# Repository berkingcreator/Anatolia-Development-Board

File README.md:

# Anatolia Geliştirme Kart Serisi

**Anatolia Geliştirme Kart Serisi**, açık kaynaklı mikrodenetleyici mimarilerini ve AVR (ATmega ve ATtiny) çekirdeklerini temel alan, yerli ve modüler bir geliştirme donanımı ailesidir. Düşük güç tüketimi gerektiren gömülü sistemlerden lojik devre simülasyonlarına, giyilebilir teknolojilerden hafif otonom modüllere kadar geniş bir yelpazede esnek çözümler sunar.

---

## 🚀 Öne Çıkan Özellikler

* **Açık Kaynak Donanım & Mimari:** Tamamen açık kaynaklı şematik ve donanım tasarımı ile özelleştirilebilir yapı.
* **Geniş Çekirdek Desteği:** İhtiyaca göre ölçeklenebilen ATmega328P ve ATtiny85 / ATtiny84 tabanlı yüksek verimli mikrodenetleyici entegrasyonu.
* **Kompakt Form Faktörü:** Minimal alan kaplayan, breadboard ve özel PCB uygulamalarına kolayca entegre edilebilir yapı.
* **Dahili Bootloader Desteği:** Optiboot ve Micronucleus / V-USB bootloader destekleri sayesinde harici programlayıcıya ihtiyaç duymadan USB üzerinden doğrudan kod yükleme.
* **Esnek G/Ç (GPIO) ve PWM:** Kart boyutuna göre optimize edilmiş dahili ADC okuma, SPI/I2C haberleşme ve PWM çıkış yeteneği.

---

## 🛠️ Kart Modelleri

* **Anatolia UNO R1 (ATmega328P):** Serinin temel amiral gemisi. Karmaşık prototipleme süreçleri, sensör ağları ve geniş G/Ç (GPIO) kapasitesi gerektiren standart projeler için geliştirilmiş çok yönlü ana geliştirme kartı.
* **Anatolia Kart G (ATtiny2313A):** Serinin 6 gen şeklindeki kartı. Giyilebilir teknolojiler için ideal.
* **Anatolia Pro Mini (ATtiny85):** Düşük güç tüketimi ve alan kısıtlaması olan gömülü projeler ile özel PCB tasarımlarına doğrudan entegre edilmek için ideal, ultra kompakt geliştirme modülü.
* **Anatolia Micro (ATtiny85):** Giyilebilir teknolojiler, minyatür sistemler ve doğrudan USB programlama gerektiren hızlı pratik çözümler için optimize edilmiş mikro boyutlu kart.
* **Anatolia Lite (ATtiny44A):** Serinin en küçük üyesi. Micro USB. Arduino İDE uyumlu.
* **Anatolia Nano (ATtiny2313A):** Nano boyutlarında tam güç!
*  **Anatolia Micro R2 (ATmega328P):** Anatolia Uno'nun gücü küçük bir kartta! Küçük projeler için ideal.

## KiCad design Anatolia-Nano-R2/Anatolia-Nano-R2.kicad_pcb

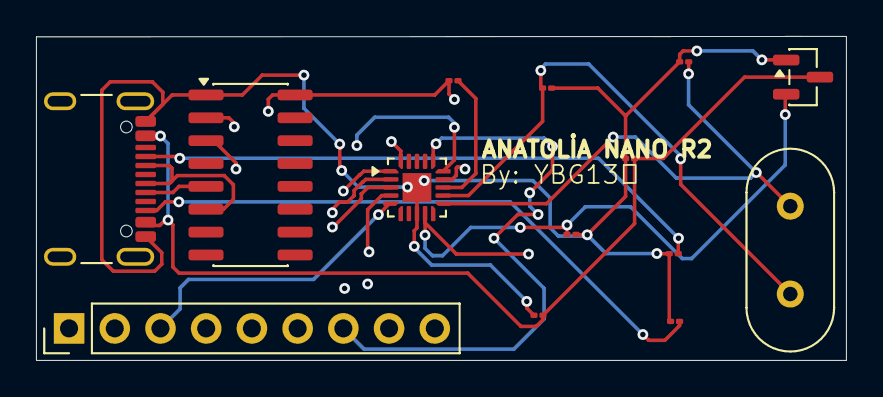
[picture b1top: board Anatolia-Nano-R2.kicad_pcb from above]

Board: 4 copper layers, 45.0 x 18.0 mm, 14 parts (0 on the bottom side), 19 nets.

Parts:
C1, C2: 22pF; C_01005_0402Metric
C3: 100nF; C_01005_0402Metric
C4, C5: 1µF; C_01005_0402Metric
J1: USB_C_Receptacle_USB2.0_16P; USB_C_Receptacle_GCT_USB4105-xx-A_16P_TopMnt_Horizontal
J2: Conn_01x09; PinHeader_1x09_P2.54mm_Vertical
R1: 10k; R_01005_0402Metric
R2, R3: 5.1k; R_01005_0402Metric
U1: ATtiny841-MM; QFN-20-1EP_3x3mm_P0.45mm_EP1.6x1.6mm
U2: CH340G; SOIC-16_3.9x9.9mm_P1.27mm
U3: MCP1700x-330xxTT; SOT-23
Y1: 8MHz; Crystal_HC49-4H_Vertical

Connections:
GND: C1.1, C2.2, C3.1, C4.1, C5.2, J1.A1 (GND), J1.A12 (GND), J1.B1 (GND), J1.B12 (GND), J2.2, R2.1, R3.1, U1.8 (GND), U1.21 (GND), U2.1 (GND), U3.1 (GND)
unnamed: J1.A5 (CC1), R2.2
unnamed: J1.B5 (CC2), R3.2
unnamed: C5.1, J2.1, R1.1, U1.9 (VCC), U2.16 (VCC), U3.2 (VO)
unnamed: J2.3, U1.5 (AREF/PA0)
unnamed: J2.4, U1.2 (PA3)
unnamed: J2.5, U1.1 (PA4)
unnamed: J2.6, U1.20 (PA5)
unnamed: J2.7, U1.16 (PA6)
unnamed: J2.8, U1.15 (PA7)
unnamed: J2.9, U1.14 (PB2)
unnamed: U1.4 (PA1), U2.3 (RXD)
unnamed: U1.3 (PA2), U2.2 (TXD)
unnamed: C1.2, U1.11 (XTAL1/PB0), Y1.2
unnamed: C2.1, U1.12 (XTAL2/PB1), Y1.1
unnamed: R1.2, U1.13 (~RESET/PB3)
unnamed: J1.A6 (D+), J1.B6 (D+), U2.5 (UD+)
unnamed: J1.A7 (D-), J1.B7 (D-), U2.6 (UD-)
VCC: C3.2, C4.2, J1.A4 (VBUS), J1.A9 (VBUS), J1.B4 (VBUS), J1.B9 (VBUS), U3.3 (VI)

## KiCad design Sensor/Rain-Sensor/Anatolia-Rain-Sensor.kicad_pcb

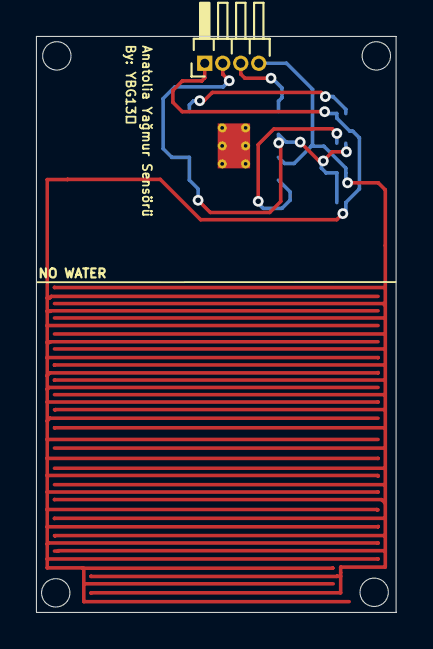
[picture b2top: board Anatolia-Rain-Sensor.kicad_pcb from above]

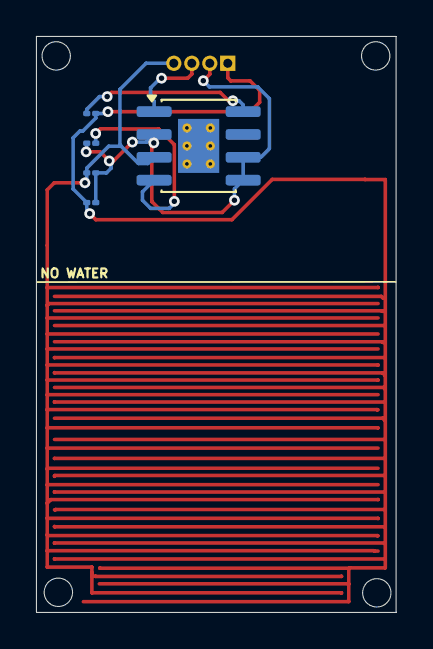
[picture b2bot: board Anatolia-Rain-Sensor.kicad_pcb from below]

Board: 2 copper layers, 20.0 x 32.0 mm, 6 parts (5 on the bottom side), 6 nets.

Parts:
C1, C2: 100nF; C_01005_0402Metric
J1: Conn_01x04_Pin; PinHeader_1x04_P1.00mm_Horizontal
R1, R2: 10K; R_01005_0402Metric
U1: LM393; SOIC-8-1EP_3.9x4.9mm_P1.27mm_EP2.29x3mm_ThermalVias

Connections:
/3: J1.4, R1.1, U1.3 (+)
/D0: J1.3, U1.1
GND: C2.1, J1.2, R1.2, R2.2, U1.2 (-), U1.5 (+), U1.6 (-)
unnamed: C1.1, U1.8 (V+)
unnamed: C2.2, U1.4 (V-)
VCC: C1.2, J1.1, R2.1

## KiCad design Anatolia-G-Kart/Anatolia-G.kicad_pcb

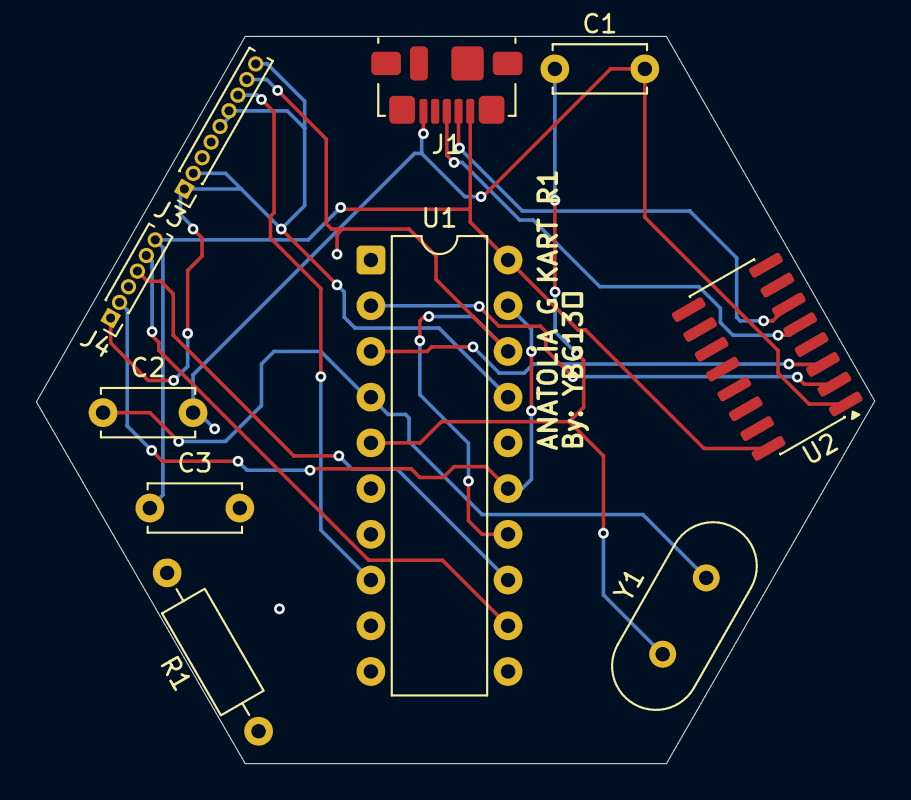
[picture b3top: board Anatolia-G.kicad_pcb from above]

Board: 4 copper layers, 46.6 x 40.4 mm, 10 parts (0 on the bottom side), 15 nets.

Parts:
C1, C2: 22pF; C_Disc_D5.0mm_W2.5mm_P5.00mm
C3: 100nF; C_Disc_D5.0mm_W2.5mm_P5.00mm
J1: USB_B_Micro; USB_Micro-B_Molex_47346-0001
J3: Conn_01x09_Pin; PinHeader_1x09_P1.00mm_Vertical
J4: Conn_01x06_Pin; PinHeader_1x06_P1.00mm_Vertical
R1: 10k; R_Axial_DIN0207_L6.3mm_D2.5mm_P10.16mm_Horizontal
U1: ATtiny2313A-P; DIP-20_W7.62mm
U2: CH340G; SOIC-16_3.9x9.9mm_P1.27mm
Y1: Crystal; Crystal_HC49-4H_Vertical

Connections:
unnamed: J1.3 (D+), U2.5 (UD+)
unnamed: J1.2 (D-), U2.6 (UD-)
unnamed: C1.2, C2.2, C3.2, J1.5 (GND), U1.10 (GND), U2.1 (GND)
unnamed: C3.1, J1.1 (VBUS), J4.6, R1.2, U1.20 (VCC), U2.16 (VCC)
unnamed: J3.1, J3.2, J3.5, J3.6, J3.9, J4.1, U1.16 (PB4), U1.17 (PB5)
unnamed: J3.7, U1.8 (PD4)
unnamed: J3.8, J4.3, U1.14 (PB2), U1.18 (PB6)
unnamed: J4.2, U1.15 (PB3), U1.19 (PB7)
unnamed: J4.4, U1.13 (PB1)
unnamed: J4.5, U1.12 (PB0)
unnamed: C1.1, U1.5 (PA0/XTAL1), Y1.1
unnamed: C2.1, U1.4 (PA1/XTAL2), Y1.2
unnamed: R1.1, U1.1 (PA2/~RESET)
unnamed: U1.2 (PD0), U2.2 (TXD)
unnamed: U1.3 (PD1), U2.3 (RXD)

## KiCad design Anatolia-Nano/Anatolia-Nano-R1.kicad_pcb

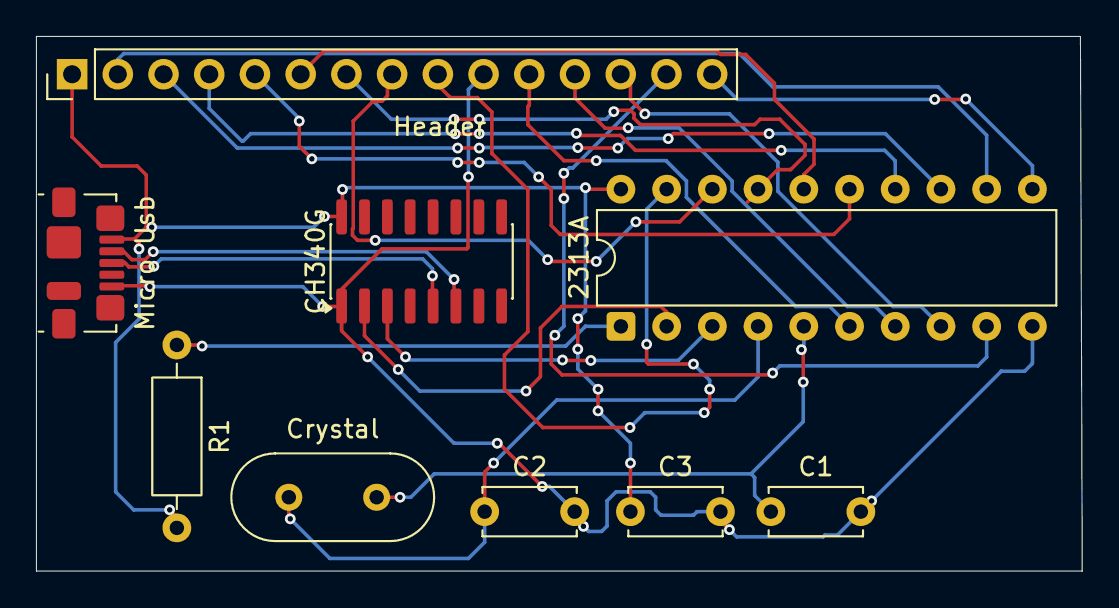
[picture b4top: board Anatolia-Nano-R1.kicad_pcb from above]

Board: 2 copper layers, 58.1 x 29.7 mm, 9 parts (0 on the bottom side), 22 nets.

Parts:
2313A: ATtiny2313A-P; DIP-20_W7.62mm
C1, C2: 22pF; C_Disc_D5.0mm_W2.5mm_P5.00mm
C3: 100nF; C_Disc_D5.0mm_W2.5mm_P5.00mm
CH340G: CH340G; SOIC-16_3.9x9.9mm_P1.27mm
Crystal: Crystal; Crystal_HC49-4H_Vertical
Header: Conn_01x15; PinHeader_1x15_P2.54mm_Vertical
Micro Usb: USB_B_Micro; USB_Micro-B_Molex_47346-0001
R1: 10k; R_Axial_DIN0207_L6.3mm_D2.5mm_P10.16mm_Horizontal

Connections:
unnamed: CH340G.5 (UD+), Micro Usb.3 (D+)
unnamed: CH340G.6 (UD-), Micro Usb.2 (D-)
unnamed: 2313A.10 (GND), C1.2, C2.2, C3.2, CH340G.1 (GND), Header.10, Micro Usb.5 (GND)
unnamed: 2313A.20 (VCC), C3.1, CH340G.16 (VCC), Header.1, Micro Usb.1 (VBUS), R1.2
unnamed: 2313A.12 (PB0), Header.2
unnamed: 2313A.13 (PB1), Header.3
unnamed: 2313A.14 (PB2), Header.4
unnamed: 2313A.15 (PB3), Header.5
unnamed: 2313A.16 (PB4), Header.6
unnamed: 2313A.17 (PB5), Header.7
unnamed: 2313A.18 (PB6), Header.8
unnamed: 2313A.19 (PB7), Header.9
unnamed: 2313A.6 (PD2), Header.11
unnamed: 2313A.7 (PD3), Header.12
unnamed: 2313A.8 (PD4), Header.13
unnamed: 2313A.9 (PD5), Header.14
unnamed: 2313A.11 (PD6), Header.15
unnamed: 2313A.5 (PA0/XTAL1), C1.1, Crystal.1
unnamed: 2313A.4 (PA1/XTAL2), C2.1, Crystal.2
unnamed: 2313A.1 (PA2/~RESET), R1.1
unnamed: 2313A.2 (PD0), CH340G.2 (TXD)
unnamed: 2313A.3 (PD1), CH340G.3 (RXD)

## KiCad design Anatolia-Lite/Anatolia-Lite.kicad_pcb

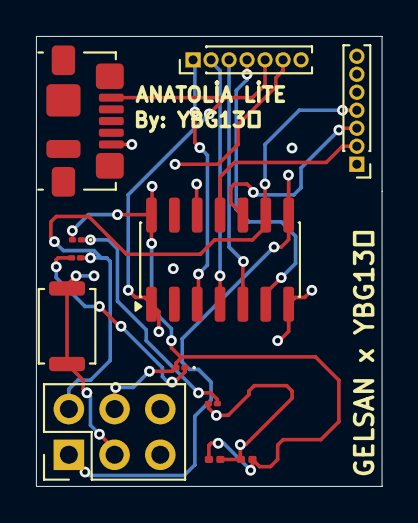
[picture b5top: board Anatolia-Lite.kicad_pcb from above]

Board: 4 copper layers, 19.2 x 25.0 mm, 12 parts (0 on the bottom side), 14 nets.

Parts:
C1: 22 µF; C_0201_0603Metric
C2: 0.022 µF; C_0201_0603Metric
D1: CLK; LED_01005_0402Metric
D2: PWR; LED_01005_0402Metric
IC1: ATTINY44A-SSU; SOIC-14_3.9x8.7mm_P1.27mm
ICSP1: M20-9740346; PinHeader_2x03_P2.54mm_Vertical
J1, J2: 7pin-2.54MaleHeader; PinHeader_1x07_P1.00mm_Vertical
R1, R2: 1k; R_01005_0402Metric
RESET1: B3FS-1012P; SW_Push_SPST_NO_Alps_SKRK
USB1: 10118193-0001LF; USB_Micro-B_Molex_47346-0001

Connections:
/PA1: IC1.12 (PA1/ADC1/AIN0/PCINT1), J2.1
/PA2: IC1.11 (PA2/ADC2/AIN1/PCINT2), J2.2
/PA3: IC1.10 (PA3/ADC3/T0/PCINT3), J2.3
/PA4/SCL: IC1.9 (PA4/ADC4/USCK/SCL/T1/PCINT4), ICSP1.2, J2.4, R1.1
/PA5/MISO: IC1.8 (PA5/ADC5/DO/MISO/OC1B/PCINT5), ICSP1.1, J2.5
/PA6/MOSI: IC1.7 (PA6/PCINT6/OC1A/SDA/MOSI/DI/ADC6), ICSP1.5, J2.6
/PA7: IC1.6 (PA7/PCINT7/ICP/OC0B/ADC7), J1.4
/PB1: IC1.3 (PB1/PCINT9/XTAL2), J1.1
/PB2: IC1.5 (PB2/PCINT10/INT0/OC0A/CKOUT), J1.3
/RESET: IC1.4 (PB3/PCINT11/~RESET/dW), ICSP1.3, J1.2, RESET1.1, RESET1.2
/VCC: C1.1, C2.2, IC1.1 (VCC), ICSP1.6, J1.5, R2.2, USB1.1 (VCC)
GND: C1.2, C2.1, D1.2, D2.2, IC1.14 (GND), ICSP1.4, J1.6, USB1.5 (GND)
unnamed: D1.1, R1.2
unnamed: D2.1, R2.1

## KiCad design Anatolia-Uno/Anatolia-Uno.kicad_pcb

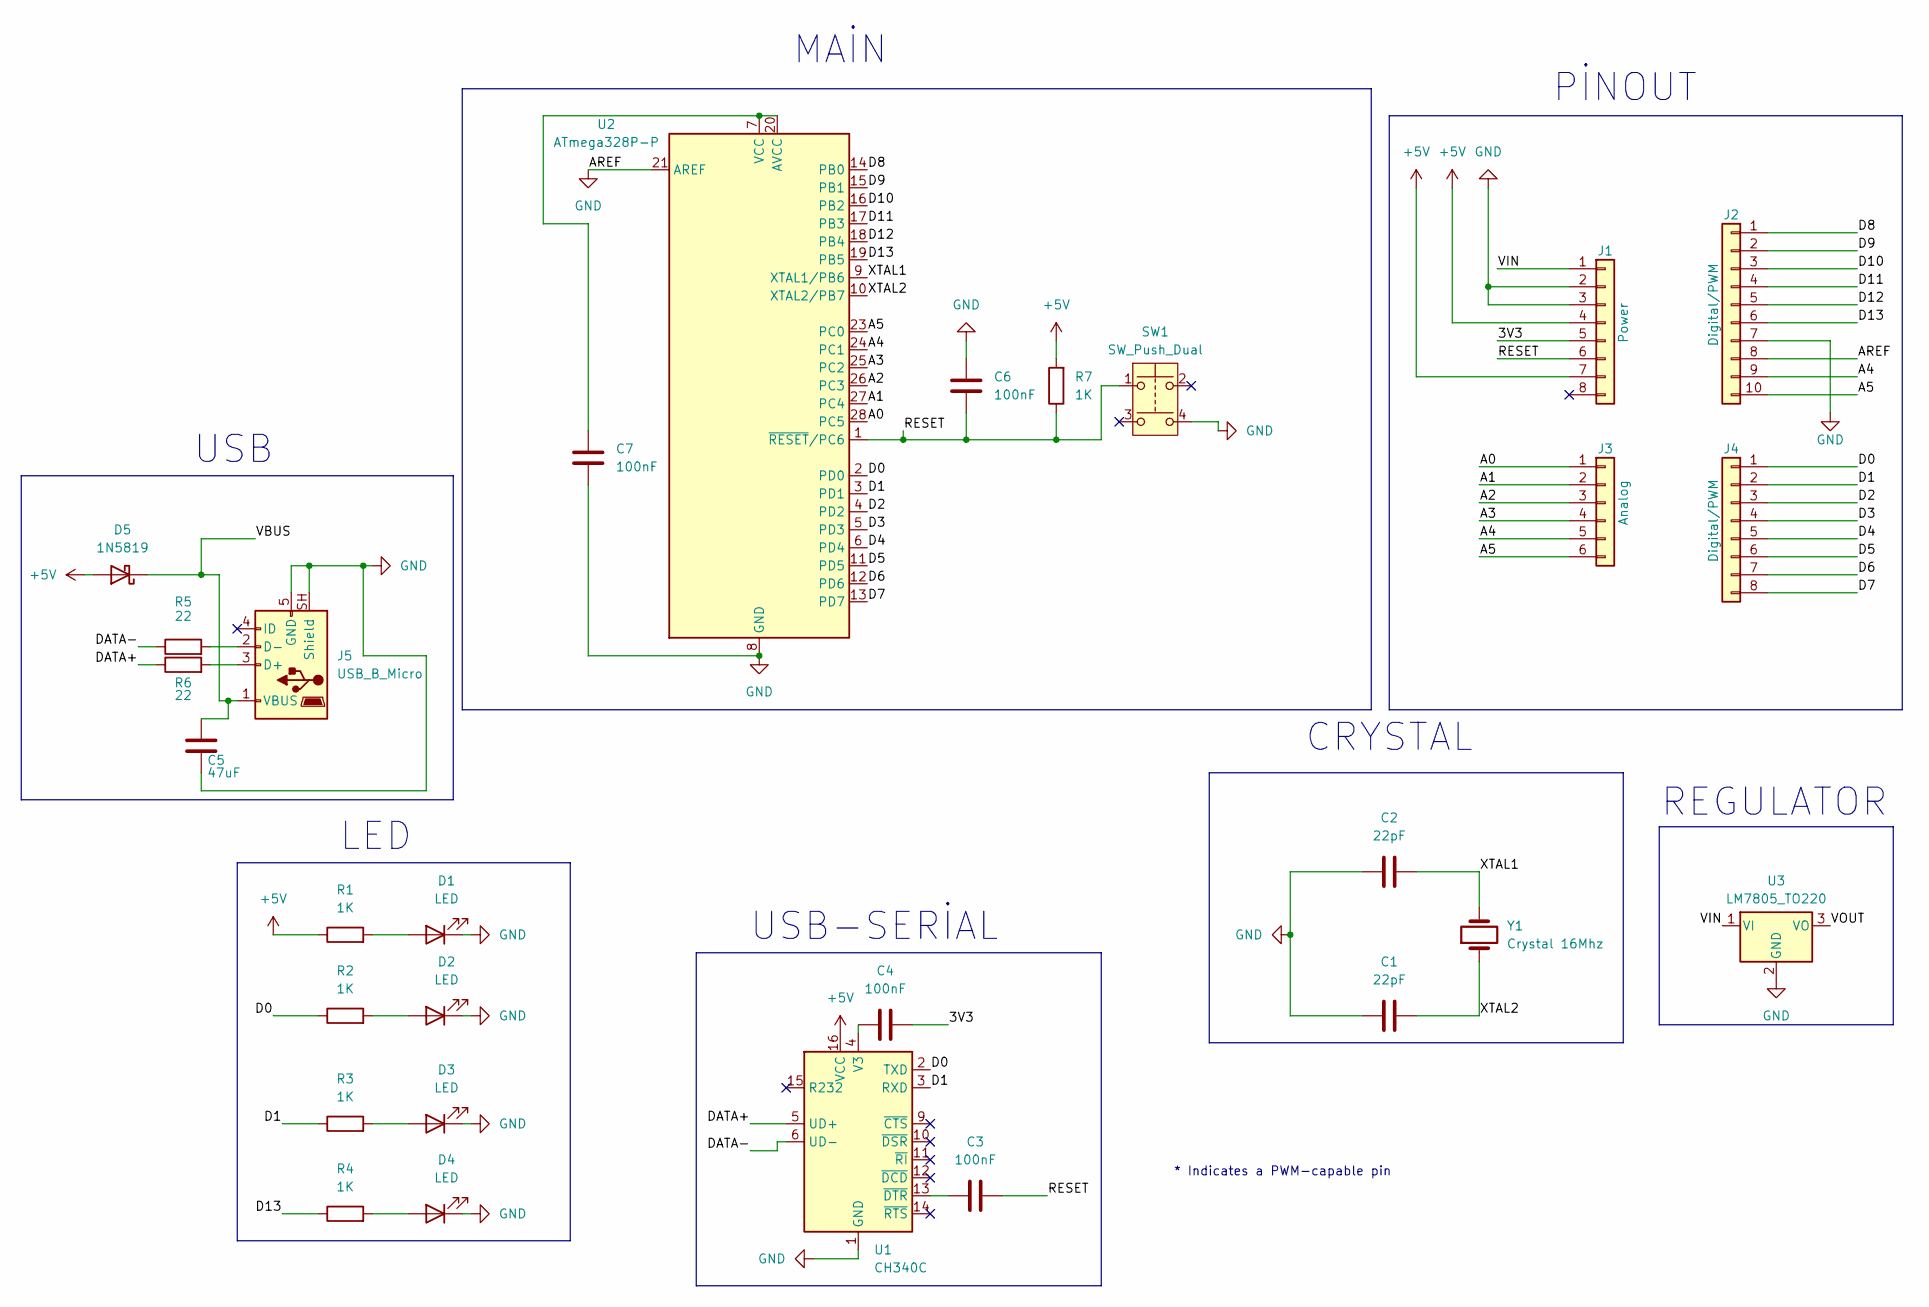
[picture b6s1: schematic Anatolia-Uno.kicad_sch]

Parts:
C1, C2: 22pF; C_01005_0402Metric
C3, C4, C6, C7: 100nF; C_01005_0402Metric
C5: 47uF; C_01005_0402Metric
D1, D2, D3, D4: LED; LED_Cree-XHP50_6V_HighDensity
D5: 1N5819; D_DO-41_SOD81_P10.16mm_Horizontal
J1: Power; PinSocket_1x08_P2.54mm_Vertical
J2: Digital/PWM; PinSocket_1x10_P2.54mm_Vertical
J3: Analog; PinSocket_1x06_P2.54mm_Vertical
J4: Digital/PWM; PinSocket_1x08_P2.54mm_Vertical
J5: USB_B_Micro; USB_Micro-B_Molex_47346-0001
R1, R2, R3: 1K; R_2816_7142Metric
R4, R7: 1K; R_0402_1005Metric
R5, R6: 22; R_0402_1005Metric
SW1: SW_Push_Dual; SW_PUSH-12mm_Wuerth-430476085716
U1: CH340C; SOIC-16_3.9x9.9mm_P1.27mm
U2: ATmega328P-P; DIP-28_W7.62mm
U3: LM7805_TO220; TO-220-3_Vertical
Y1: Crystal 16Mhz; Crystal_HC49-U-3Pin_Vertical

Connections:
+5V: D5.2 (A), J1.4, J1.7, R1.1, R7.2, U1.16 (VCC)
/3V3: C4.2, J1.5
/A0: J3.1, U2.28 (PC5)
/A1: J3.2, U2.27 (PC4)
/A2: J3.3, U2.26 (PC3)
/A3: J3.4, U2.25 (PC2)
/A4: J2.9, J3.5, U2.24 (PC1)
/A5: J2.10, J3.6, U2.23 (PC0)
/D0: J4.1, R2.1, U1.2 (TXD), U2.2 (PD0)
/D1: J4.2, R3.1, U1.3 (RXD), U2.3 (PD1)
/D2: J4.3, U2.4 (PD2)
/D3: J4.4, U2.5 (PD3)
/D4: J4.5, U2.6 (PD4)
/D5: J4.6, U2.11 (PD5)
/D6: J4.7, U2.12 (PD6)
/D7: J4.8, U2.13 (PD7)
/D8: J2.1, U2.14 (PB0)
/D9: J2.2, U2.15 (PB1)
/D10: J2.3, U2.16 (PB2)
/D11: J2.4, U2.17 (PB3)
/D12: J2.5, U2.18 (PB4)
/D13: J2.6, R4.1, U2.19 (PB5)
/DATA+: R6.1, U1.5 (UD+)
/DATA-: R5.1, U1.6 (UD-)
/RESET: C3.2, C6.1, J1.6, R7.1, SW1.1 (1_1), U2.1 (~RESET/PC6)
/VBUS: C5.1, D5.1 (K), J5.1 (VBUS)
/VIN: J1.1, U3.1 (VI)
/VOUT: U3.3 (VO)
/XTAL1: C2.2, U2.9 (XTAL1/PB6), Y1.2
/XTAL2: C1.2, U2.10 (XTAL2/PB7), Y1.1
GND: C1.1, C2.1, C5.2, C6.2, C7.2, D1.1 (K), D2.1 (K), D3.1 (K), D4.1 (K), J1.2, J1.3, J2.7, J2.8, J5.5 (GND), J5.SH (Shield), SW1.4 (2_2), U1.1 (GND), U2.8 (GND), U2.21 (AREF), U2.22 (GND), U3.2 (GND)
unnamed: D1.2 (A), R1.2
unnamed: D2.2 (A), R2.2
unnamed: D3.2 (A), R3.2
unnamed: D4.2 (A), R4.2
unnamed: J5.3 (D+), R6.2
unnamed: J5.2 (D-), R5.2
unnamed: C4.1, U1.4 (V3)
unnamed: C3.1, U1.13 (~DTR)
unnamed: C7.1, U2.7 (VCC), U2.20 (AVCC)

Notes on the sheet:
MAİN
REGULATOR
USB-SERİAL
USB
CRYSTAL
PİNOUT
LED
* Indicates a PWM-capable pin

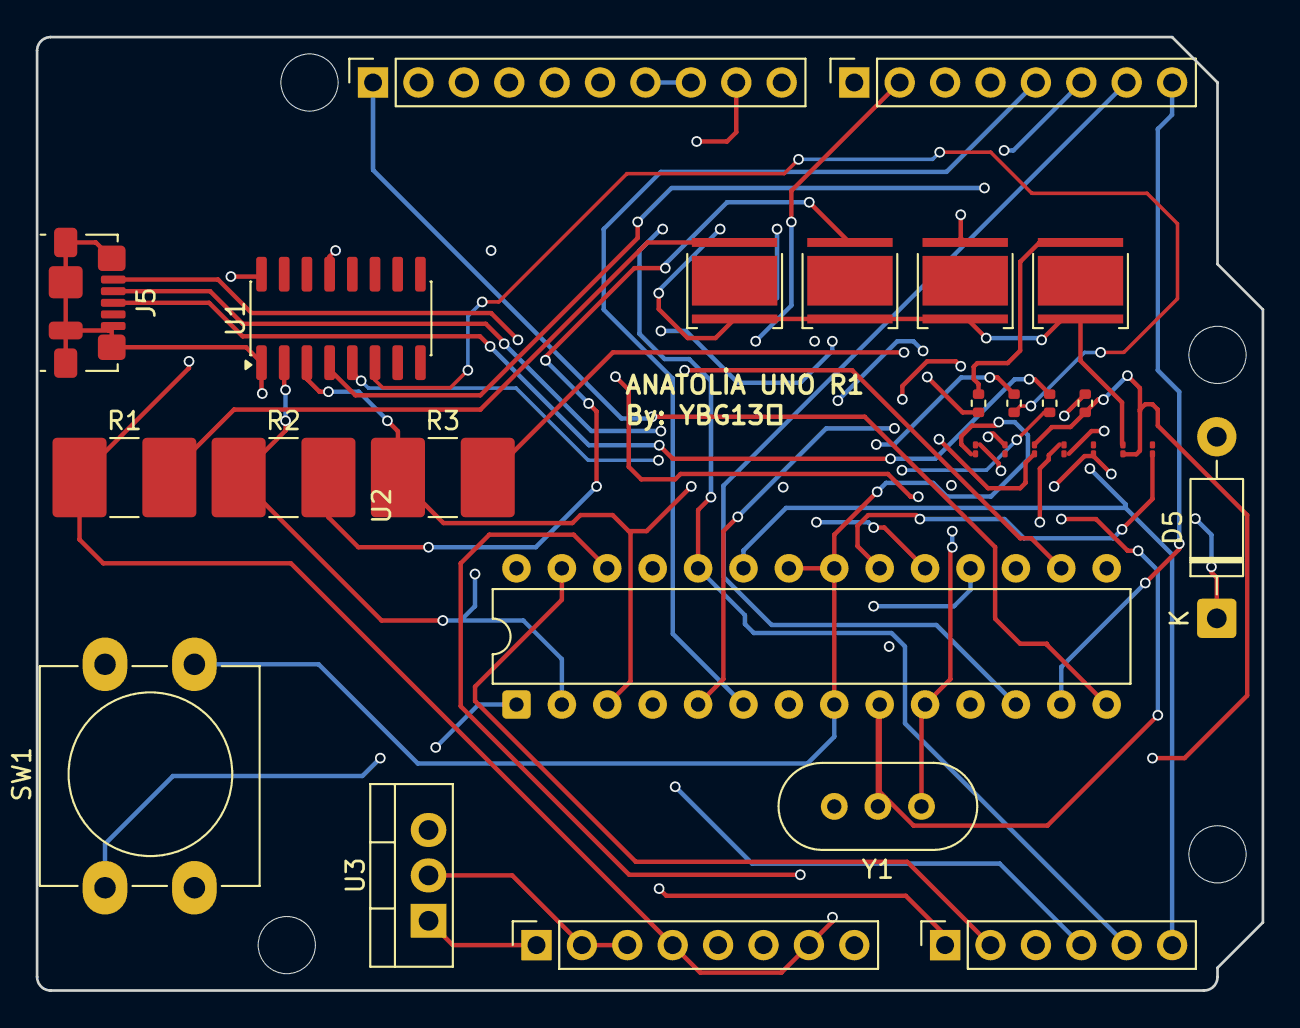
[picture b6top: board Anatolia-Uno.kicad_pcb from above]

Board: 4 copper layers, 68.6 x 53.3 mm, 33 parts (0 on the bottom side), 39 nets.

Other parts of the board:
MH1, MH2, MH3, MH4: MountingHole_3.2mm

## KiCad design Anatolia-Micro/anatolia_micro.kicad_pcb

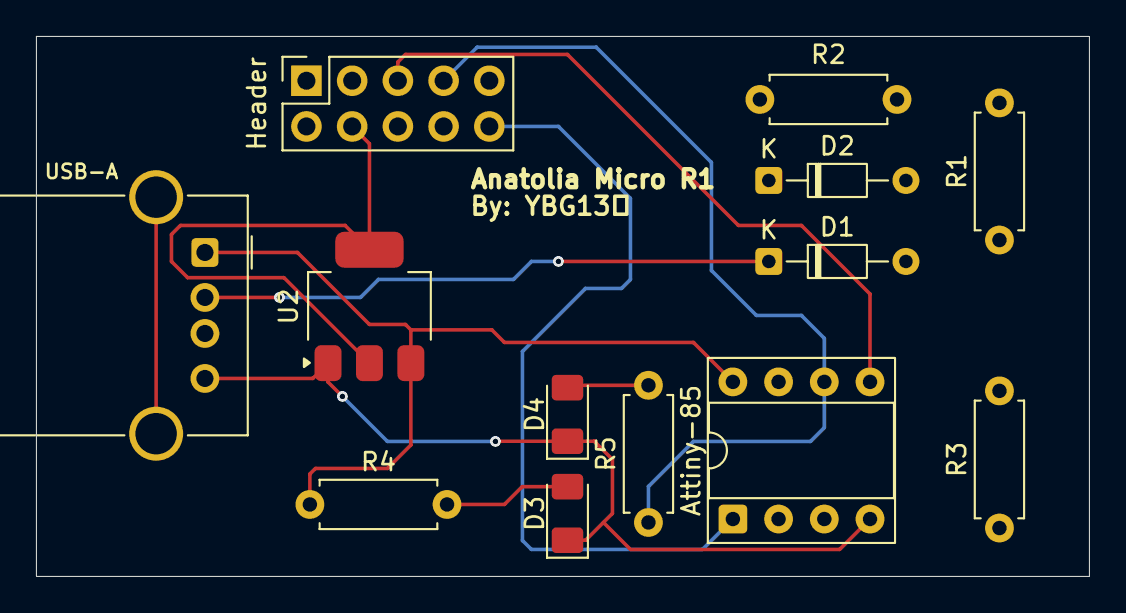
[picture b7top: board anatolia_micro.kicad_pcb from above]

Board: 4 copper layers, 58.5 x 30.0 mm, 13 parts (0 on the bottom side), 13 nets.

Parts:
Attiny-85: ATtiny85-20P; DIP-8_W7.62mm_Socket
D1, D2: 3.6 Zener; D_DO-34_SOD68_P7.62mm_Horizontal
D3, D4: LED; LED_1206_3216Metric_Pad1.42x1.75mm_HandSolder
Header: Conn; PinSocket_2x05_P2.54mm_Vertical
R1: 1K5; R_Axial_DIN0207_L6.3mm_D2.5mm_P7.62mm_Horizontal
R2, R3 : 66; R_Axial_DIN0207_L6.3mm_D2.5mm_P7.62mm_Horizontal
R4 , R5: 470; R_Axial_DIN0207_L6.3mm_D2.5mm_P7.62mm_Horizontal
U2: AMS1117-3.3; SOT-223-3_TabPin2
USB-A: USB_A; USB_A_Molex_67643_Horizontal

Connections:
/3V3: Header.4, U2.2 (VO)
/5V: Attiny-85.8 (VCC), Header.2, R1.2, R4.1, U2.3 (VI), USB-A.1 (VBUS)
/GND: Attiny-85.4 (GND), D1.2 (A), D2.2 (A), D3.1 (K), D4.1 (K), Header.1, Header.3, U2.1 (GND), USB-A.4 (GND)
/PB0: Attiny-85.5 (AREF/PB0), Header.5
/PB1: Attiny-85.6 (PB1), Header.7, R5.1
/PB2: Attiny-85.7 (PB2), Header.9
/PB3: Attiny-85.2 (XTAL1/PB3), Header.6, R3.1
/PB4: Attiny-85.3 (XTAL2/PB4), Header.8, R2.1
/PB5: Attiny-85.1 (~RESET/PB5), Header.10
unnamed: D1.1 (K), R1.1, R3.2, USB-A.2 (D-)
unnamed: D2.1 (K), R2.2, USB-A.3 (D+)
unnamed: D3.2 (A), R4.2
unnamed: D4.2 (A), R5.2

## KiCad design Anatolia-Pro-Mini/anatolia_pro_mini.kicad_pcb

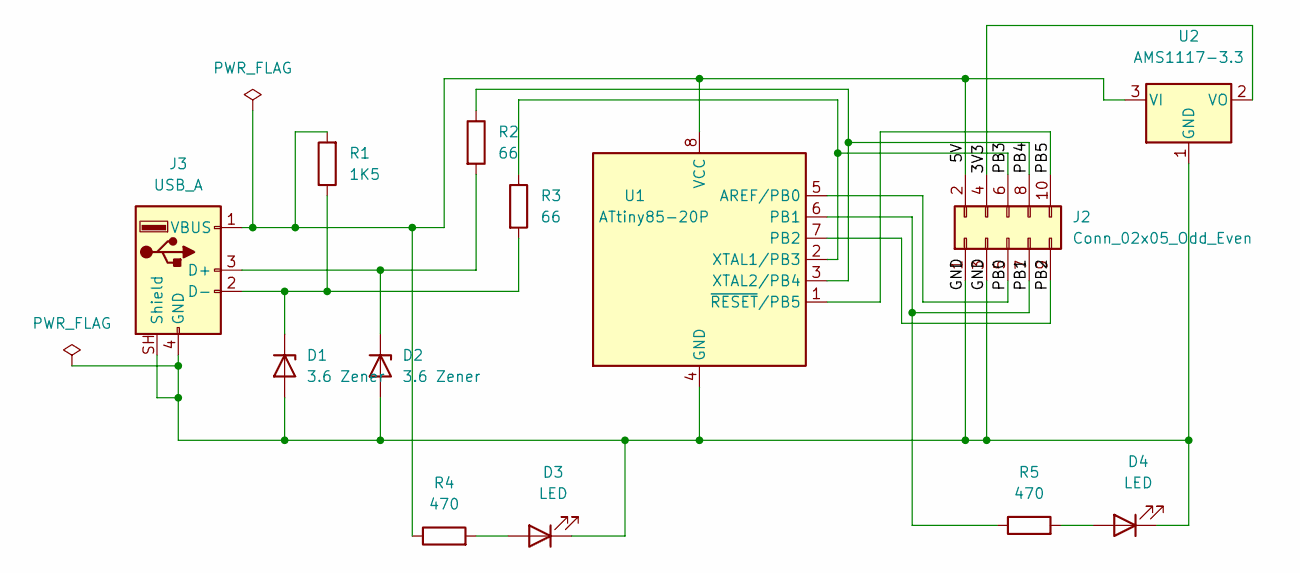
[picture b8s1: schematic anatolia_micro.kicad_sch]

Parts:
D1, D2: 3.6 Zener; D_0603_1608Metric
D3, D4: LED; LED_1206_3216Metric_Pad1.42x1.75mm_HandSolder
J2: Conn_02x05_Odd_Even; PinSocket_2x05_P2.54mm_Vertical_SMD
J3: USB_A; USB_Micro-B_Molex_47346-0001
R1: 1K5; R_01005_0402Metric
R2, R3: 66; R_01005_0402Metric
R4, R5: 470; R_01005_0402Metric
U1: ATtiny85-20P; DIP-8_W7.62mm_Socket
U2: AMS1117-3.3; SOT-223-3_TabPin2

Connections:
/3V3: J2.4, U2.2 (VO)
/5V: J2.2, J3.1 (VBUS), R1.2, R4.1, U1.8 (VCC), U2.3 (VI)
/GND: D1.2 (A), D2.2 (A), D3.1 (K), D4.1 (K), J2.1, J2.3, J3.4 (GND), J3.SH (Shield), U1.4 (GND), U2.1 (GND)
/PB0: J2.5, U1.5 (AREF/PB0)
/PB1: J2.7, R5.1, U1.6 (PB1)
/PB2: J2.9, U1.7 (PB2)
/PB3: J2.6, R3.1, U1.2 (XTAL1/PB3)
/PB4: J2.8, R2.1, U1.3 (XTAL2/PB4)
/PB5: J2.10, U1.1 (~RESET/PB5)
unnamed: D1.1 (K), J3.2 (D-), R1.1, R3.2
unnamed: D2.1 (K), J3.3 (D+), R2.2
unnamed: D3.2 (A), R4.2
unnamed: D4.2 (A), R5.2

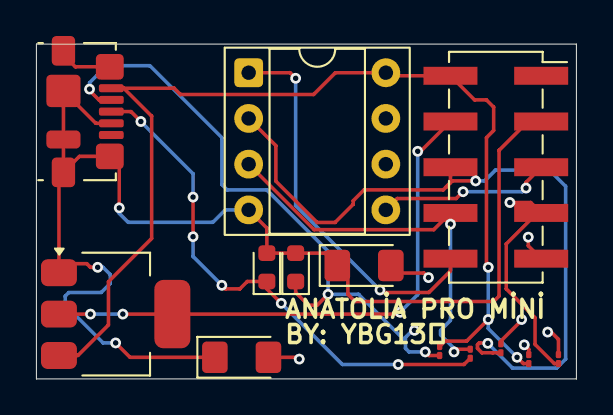
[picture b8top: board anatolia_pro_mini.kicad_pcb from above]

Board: 4 copper layers, 30.0 x 18.6 mm, 13 parts (0 on the bottom side), 13 nets.
